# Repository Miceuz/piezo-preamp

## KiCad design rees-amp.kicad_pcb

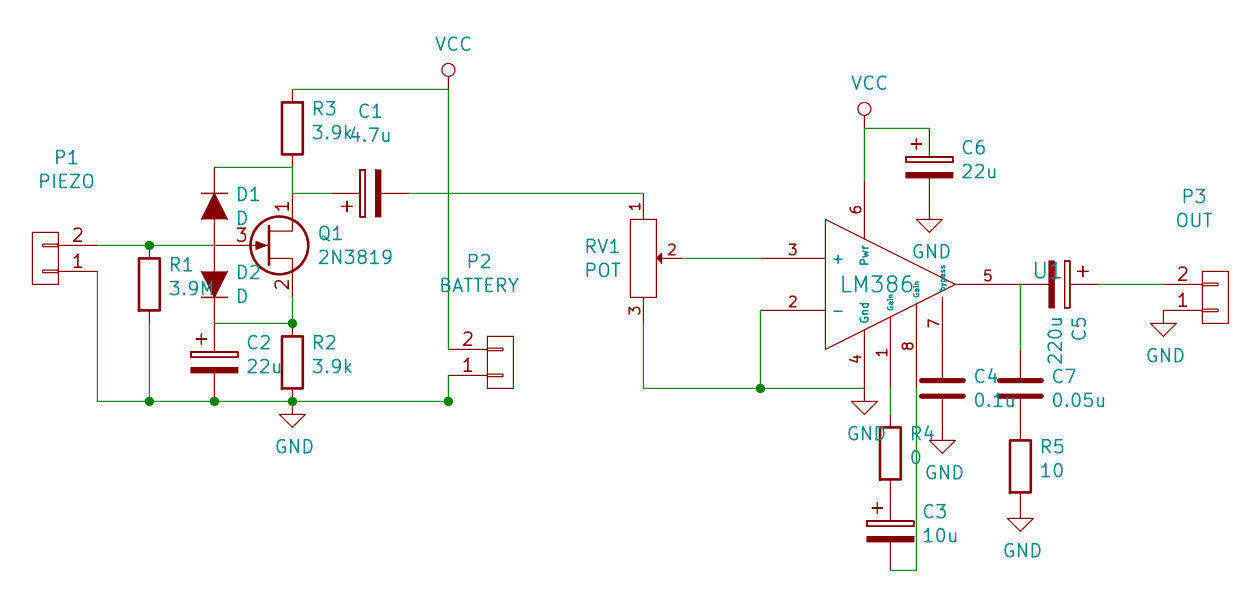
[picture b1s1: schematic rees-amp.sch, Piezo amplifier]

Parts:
C1: 4.7u; C_Radial_D5_L11_P2; PartNo ?
C2, C6: 22u; C_Radial_D5_L11_P2; PartNo ?
C3: 10u; C_Radial_D5_L11_P2; PartNo ?
C4: 0.1u; cnp_7x2mm; PartNo ?
C5: 220u; C_Radial_D5_L11_P2; PartNo ?
C7: 0.05u; cnp_3mm_disc; PartNo ?
D1, D2: D; Diode_DO-35_SOD27_Horizontal_RM10; PartNo ?
P1: PIEZO; Pin_Header_Straight_1x02; PartNo ?
P2: BATTERY; Pin_Header_Straight_1x02; PartNo ?
P3: OUT; mors_2p; PartNo ?
Q1: 2N3819; TO-92_Molded_Wide_Oval; PartNo ?
R1: 3.9M; Resistor_Horizontal_RM7mm; PartNo ?
R2, R3: 3.9k; Resistor_Horizontal_RM7mm; PartNo ?
R4: 0; Resistor_Horizontal_RM7mm; PartNo ?
R5: 10; RC03; PartNo ?
RV1: POT; Potentiometer_WirePads; PartNo ?
U1: LM386; dil_8-300_socket; PartNo ?

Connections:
GND: C2.2, C4.2, C6.2, P1.1, P2.1, P3.1, R1.2, R2.2, R5.2, RV1.3, U1.2 (-), U1.4 (Gnd)
unnamed: C1.1, D1.2 (K), Q1.1 (D), R3.1
unnamed: C1.2, RV1.1
unnamed: C2.1, D2.2 (K), Q1.2 (S), R2.1
unnamed: C3.1, R4.2
unnamed: C3.2, U1.8 (Gain)
unnamed: C4.1, U1.7 (bypass)
unnamed: C5.1, P3.2
unnamed: C5.2, C7.1, U1.5
unnamed: C7.2, R5.1
unnamed: D1.1 (A), D2.1 (A), P1.2, Q1.3 (G), R1.1
unnamed: R4.1, U1.1 (Gain)
unnamed: RV1.2, U1.3 (+)
VCC: C6.1, P2.2, R3.2, U1.6 (Pwr)

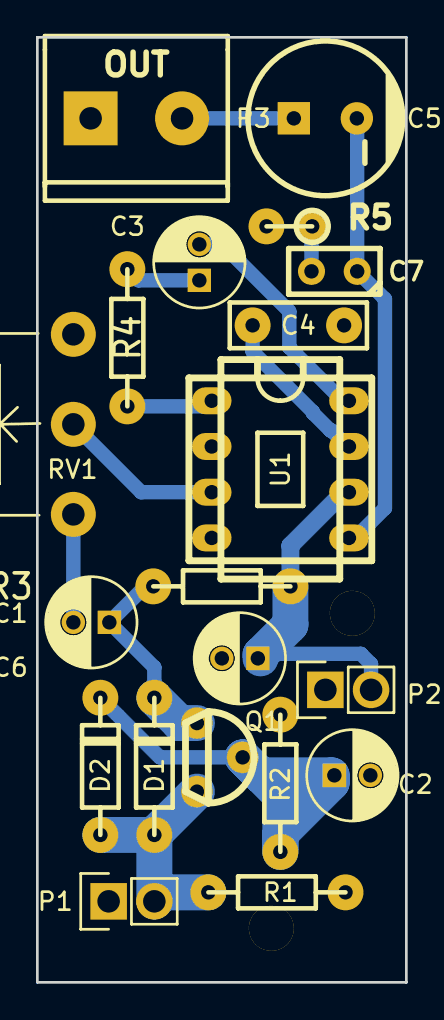
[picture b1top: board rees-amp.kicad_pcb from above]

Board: 2 copper layers, 20.5 x 52.5 mm, 20 parts (0 on the bottom side), 14 nets.

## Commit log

2018-10-22 Initial. Forgotten project being pushed to git
